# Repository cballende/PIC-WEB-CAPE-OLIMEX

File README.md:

PIC-WEB-CAPE
This project template for KICAD EDA is the basis of an expansion board 
"CAPE" for the OLIMEX PIC-WEB.
For example Olimex PIC-WEB Rev C, Rev D ect...
This base project includes a PCB edge defined as the same
size as the PIC-WEB Rev C PCB with the connectors placed
correctly to align the two boards.

Contours and holes can be easely modified, just remove line or hole
and redraw wath you want in layer "edge.cuts".
In layer "Dwgs.User" you have the position of Reset button,
POT, ICSP and Power connector, ethernet port.

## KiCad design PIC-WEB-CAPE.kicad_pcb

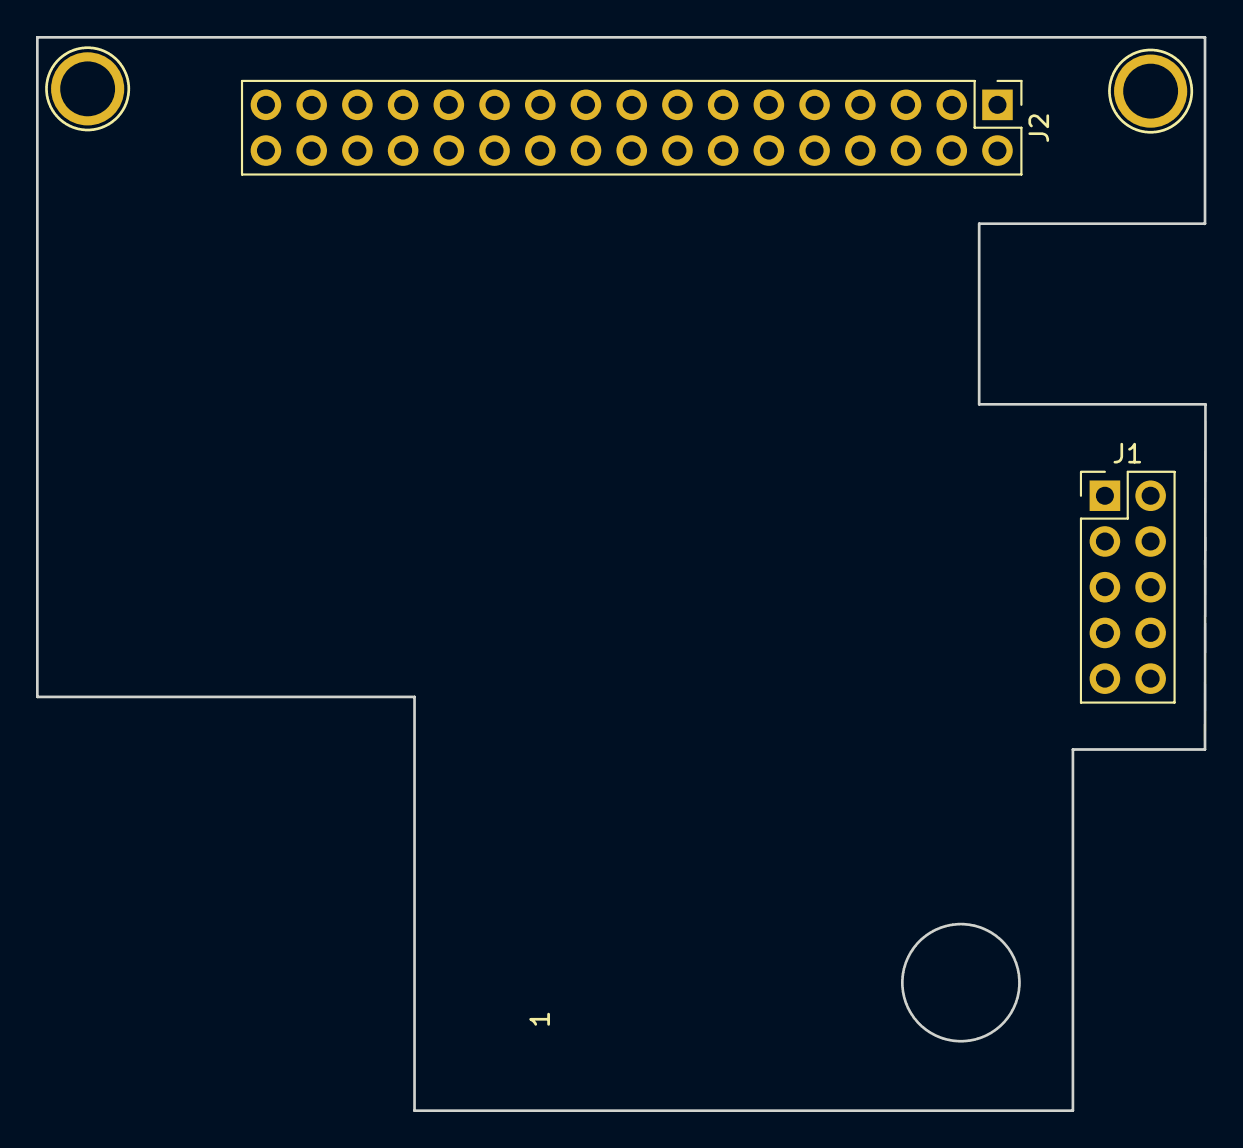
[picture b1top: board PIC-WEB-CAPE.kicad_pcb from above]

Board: 2 copper layers, 64.9 x 59.6 mm, 4 parts (0 on the bottom side), 3 nets, no tracks yet.

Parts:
J1: UEXT; PinHeader_2x05_P2.54mm_Vertical
J2: EXT; PinHeader_2x17_P2.54mm_Vertical
P7, P8: CONN_01X01; Arduino_1pin

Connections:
/+3.3V: J2.17, J2.18
/NC: J2.31, J2.32
GND: J1.2, J2.19

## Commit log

2021-04-11 Init
    add lifes
